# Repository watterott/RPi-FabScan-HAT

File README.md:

# RPi-FabScan-HAT
Raspberry Pi HAT (Hardware Attached on Top) to drive Stepper and Servo Motors or to build a 3D Laser Scanner.

Infos about the FabScan 3D-Scanner: http://www.fabscan.org

* Microchip ATmega328P with Arduino compatible Bootloader (optiboot)
* Sockets for Stepper Motor Drivers like StepStick or SilenStepStick
* Connectors for Servo Motors
* Laser control outputs
* [Raspberry Pi HAT](https://github.com/raspberrypi/hats) compatible (40 pin connector)
* Open-Source and released under the [Creative Commons Attribution Share-Alike License](https://creativecommons.org/licenses/by-sa/4.0/).
* **[Documentation on learn.watterott.com](https://learn.watterott.com)**

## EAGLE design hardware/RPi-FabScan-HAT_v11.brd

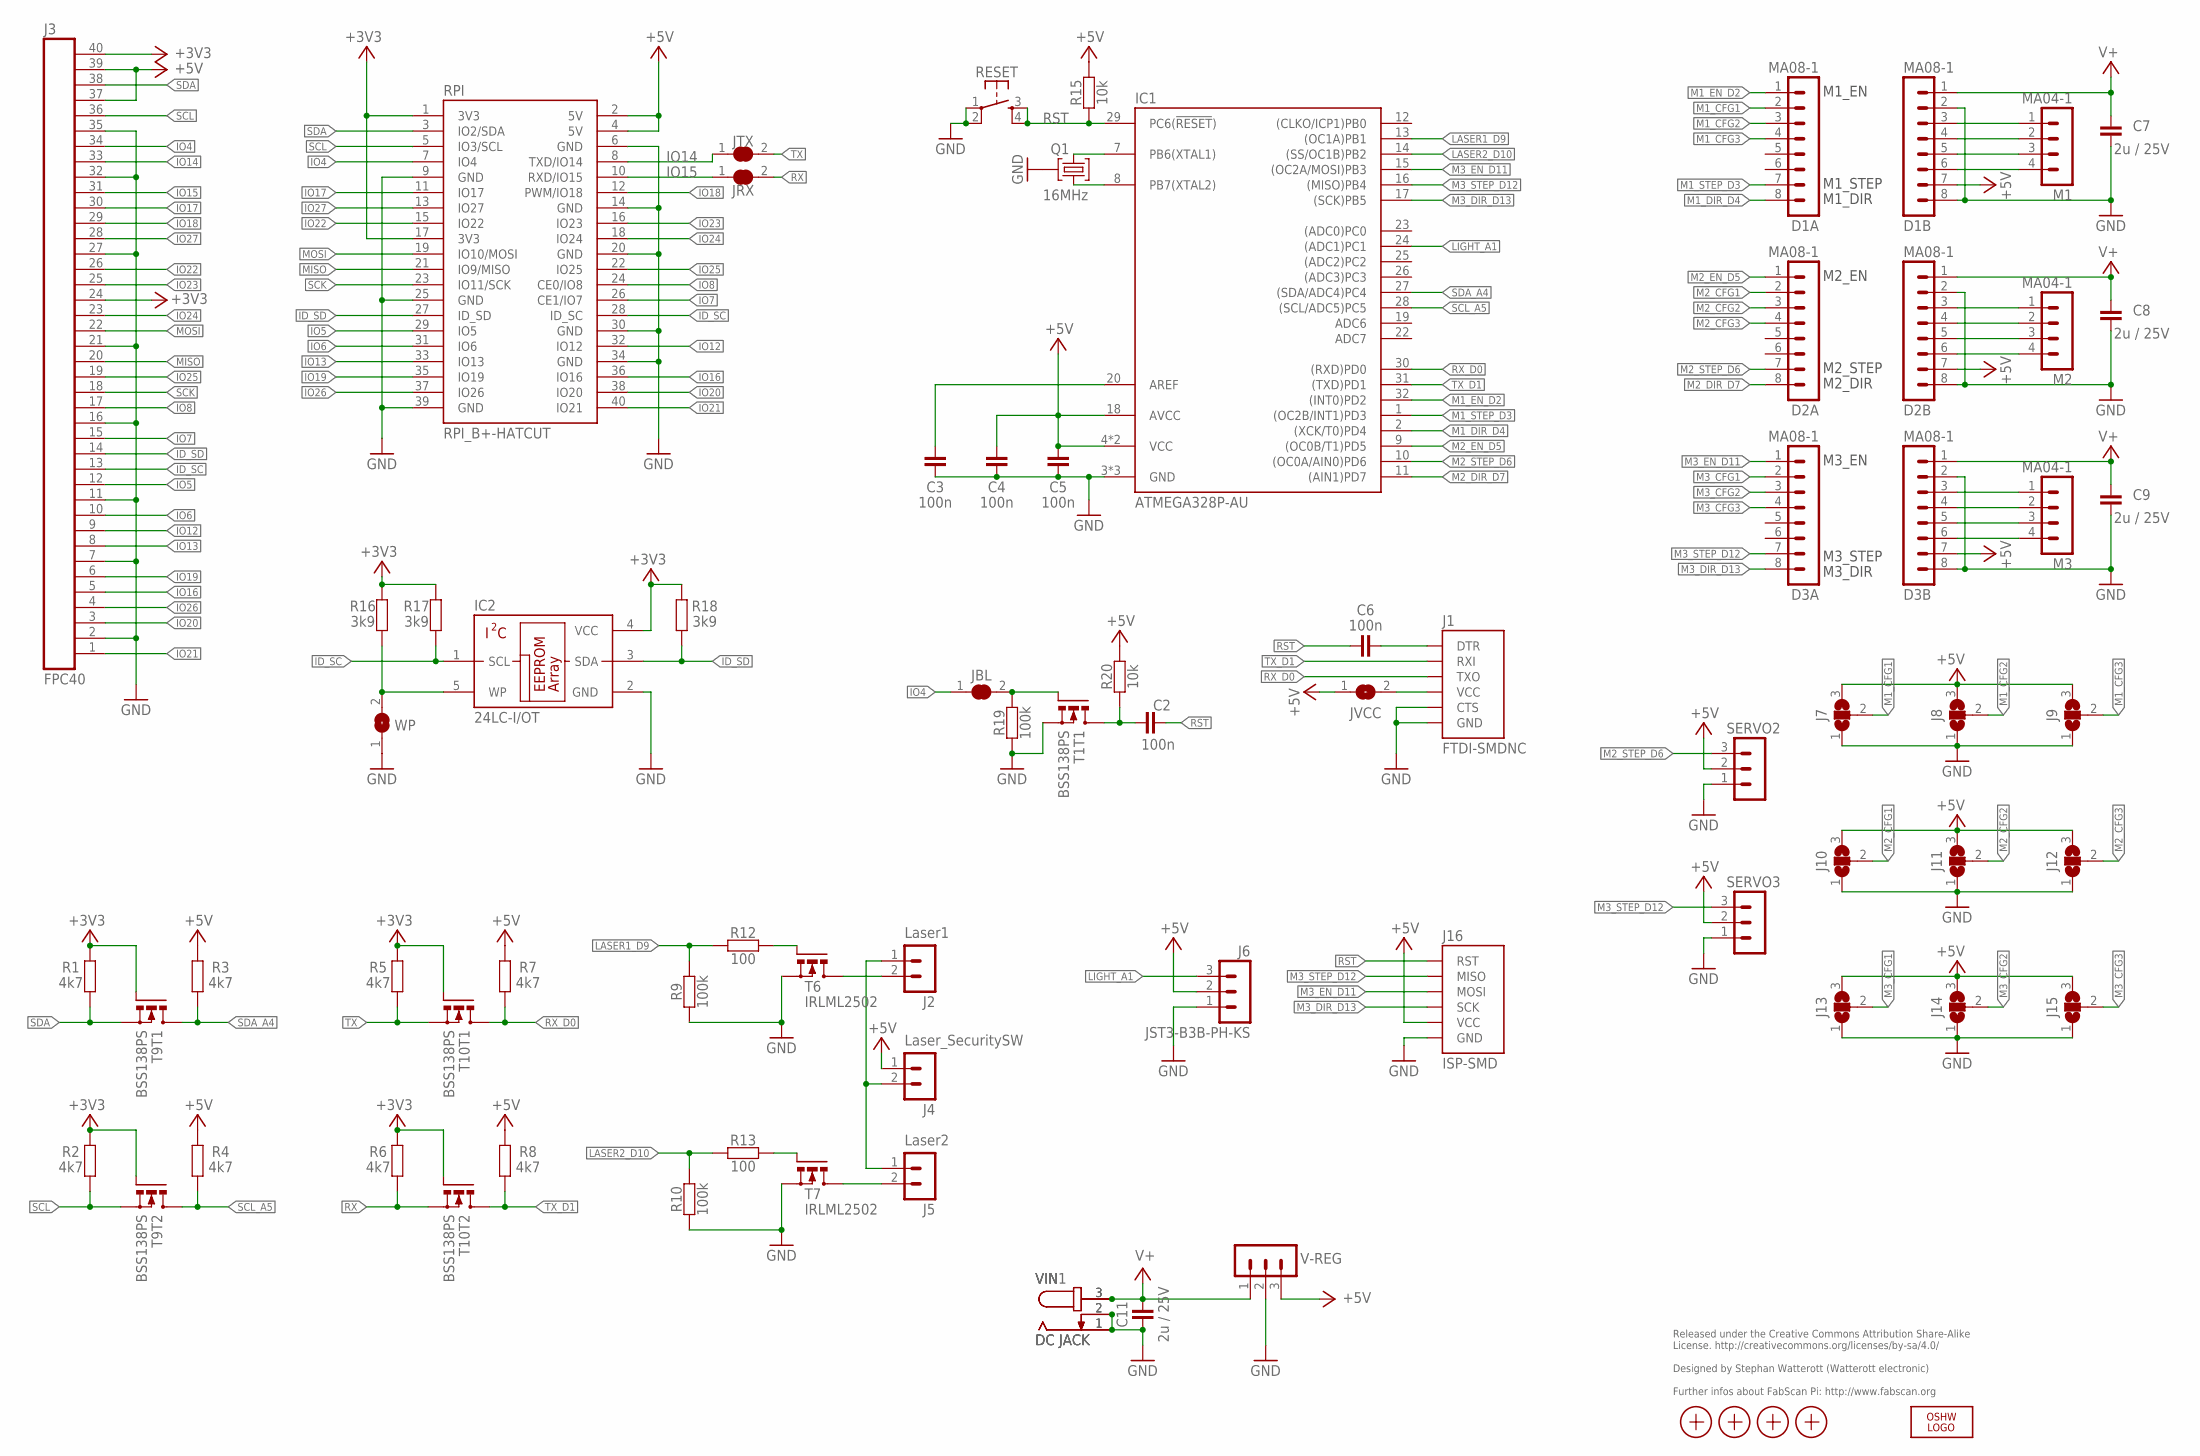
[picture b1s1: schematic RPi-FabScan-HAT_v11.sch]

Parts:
1, 2: PASSER-07; PASSER_07MM
C2, C3, C4, C5, C6: 100n; C0402
C7, C8, C9, C11: 2u / 25V; C1206
D1A, D1B, D2A, D2B, D3A, D3B: MA08-1
IC1: ATMEGA328P-AU; TQFP32
IC2: 24LC-I/OT; SOT23-5
J1: FTDI-SMDNC; FTDI_SMDNC
J2: Laser1; MA02-1
J3: FPC40; FPC40-0.5
J4: Laser_SecuritySW; MA02-1
J5: Laser2; MA02-1
J6: JST3-B3B-PH-KS; JST_B3B-PH-KS
J7, J8, J9, J10, J11, J12, J13, J14, J15: JUMPER3-0603-NC; JUMPER3-0603_NC
J16: ISP-SMD; ISP-2X3_SMD
JBL: JUMPER2-0402-NC; JUMPER2-0402_NC
JRX: JUMPER2-0402-NC; JUMPER2-0402_NC
JTX: JUMPER2-0402-NC; JUMPER2-0402_NC
JVCC: JUMPER2-0402-NC; JUMPER2-0402_NC
LOGO2: OSHW_LOGOX0100; OSHW_6X100
M1, M2, M3: MA04-1
Q1: 16MHz; CRYSTAL_32X13
R1, R2, R3, R4, R5, R6, R7, R8: 4k7; C0402
R9, R10, R19: 100k; C0402
R12, R13: 100; C0402
R15, R20: 10k; C0402
R16, R17, R18: 3k9; C0402
RESET: SW-TACTILE-PTS840P; SW_PTS840P
RPI: RPI_B+-HATCUT; RPI-B+HAT_CUTOUT
SERVO2, SERVO3: MA03-1
T1, T9, T10: BSS138PS; SOT363
T6, T7: IRLML2502; SOT23
V-REG: MA03-1
VIN, VIN1: DC JACK; DC-JACK
WP: JUMPER2-0402-NC; JUMPER2-0402_NC
X1, X4: PASSER-07; PASSER_07MM

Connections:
+3V3: IC2.4 (VCC), J3.24, J3.40, R1.1, R2.1, R5.1, R6.1, R16.2, R17.2, R18.2, RPI.1 (3V3), RPI.17 (3V3), T9.2 (G), T9.5 (G), T10.2 (G), T10.5 (G)
+5V: C4.2, C5.2, D1B.7, D2B.7, D3B.7, IC1.4 (VCC), IC1.6 (VCC), IC1.18 (AVCC), J3.37, J3.39, J4.1, J6.2, J7.3, J8.3, J9.3, J10.3, J11.3, J12.3, J13.3, J14.3, J15.3, J16.VCC, JVCC.1, R3.1, R4.1, R7.1, R8.1, R15.2, R20.2, RPI.2 (5V), RPI.4 (5V), SERVO2.2, SERVO3.2, V-REG.3
GND: C3.1, C4.1, C5.1, C7.1, C8.1, C9.1, C11.1, D1B.2, D1B.8, D2B.2, D2B.8, D3B.2, D3B.8, IC1.3 (GND), IC1.5 (GND), IC1.21 (GND), IC2.2 (GND), J1.1-GND (GND), J1.2-CTS (CTS), J3.2, J3.7, J3.11, J3.16, J3.21, J3.27, J3.32, J3.35, J6.1, J7.1, J8.1, J9.1, J10.1, J11.1, J12.1, J13.1, J14.1, J15.1, J16.GND, Q1.GND, R9.1, R10.1, R19.1, RESET.1, RESET.2, RPI.6 (GND), RPI.9 (GND), RPI.14 (GND), RPI.20 (GND), RPI.25 (GND), RPI.30 (GND), RPI.34 (GND), RPI.39 (GND), SERVO2.1, SERVO3.1, T1.1 (S), T6.2 (S), T7.2 (S), V-REG.2, VIN.1, VIN.2, VIN1.1, VIN1.2, WP.1
ID_SC: IC2.1 (SCL), J3.13, R17.1, RPI.28 (ID_SC)
ID_SD: IC2.3 (SDA), J3.14, R18.1, RPI.27 (ID_SD)
IO4: J3.34, JBL.1, RPI.7 (IO4)
IO5: J3.12, RPI.29 (IO5)
IO6: J3.10, RPI.31 (IO6)
IO7: J3.15, RPI.26 (CE1/IO7)
IO8: J3.17, RPI.24 (CE0/IO8)
IO12: J3.9, RPI.32 (IO12)
IO13: J3.8, RPI.33 (IO13)
IO14: J3.33, JTX.1, RPI.8 (TXD/IO14)
IO15: J3.31, JRX.1, RPI.10 (RXD/IO15)
IO16: J3.5, RPI.36 (IO16)
IO17: J3.30, RPI.11 (IO17)
IO18: J3.29, RPI.12 (PWM/IO18)
IO19: J3.6, RPI.35 (IO19)
IO20: J3.3, RPI.38 (IO20)
IO21: J3.1, RPI.40 (IO21)
IO22: J3.26, RPI.15 (IO22)
IO23: J3.25, RPI.16 (IO23)
IO24: J3.23, RPI.18 (IO24)
IO25: J3.19, RPI.22 (IO25)
IO26: J3.4, RPI.37 (IO26)
IO27: J3.28, RPI.13 (IO27)
LASER1_D9: IC1.13 ((OC1A)PB1), R9.2, R12.1
LASER2_D10: IC1.14 ((SS/OC1B)PB2), R10.2, R13.1
LIGHT_A1: IC1.24 ((ADC1)PC1), J6.3
M1_CFG1: D1A.2, J7.2
M1_CFG2: D1A.3, J8.2
M1_CFG3: D1A.4, J9.2
M1_DIR_D4: D1A.8, IC1.2 ((XCK/T0)PD4)
M1_EN_D2: D1A.1, IC1.32 ((INT0)PD2)
M1_STEP_D3: D1A.7, IC1.1 ((OC2B/INT1)PD3)
M2_CFG1: D2A.2, J10.2
M2_CFG2: D2A.3, J11.2
M2_CFG3: D2A.4, J12.2
M2_DIR_D7: D2A.8, IC1.11 ((AIN1)PD7)
M2_EN_D5: D2A.1, IC1.9 ((OC0B/T1)PD5)
M2_STEP_D6: D2A.7, IC1.10 ((OC0A/AIN0)PD6), SERVO2.3
M3_CFG1: D3A.2, J13.2
M3_CFG2: D3A.3, J14.2
M3_CFG3: D3A.4, J15.2
M3_DIR_D13: D3A.8, IC1.17 ((SCK)PB5), J16.SCK
M3_EN_D11: D3A.1, IC1.15 ((OC2A/MOSI)PB3), J16.MOSI
M3_STEP_D12: D3A.7, IC1.16 ((MISO)PB4), J16.MISO, SERVO3.3
MISO: J3.20, RPI.21 (IO9/MISO)
MOSI: J3.22, RPI.19 (IO10/MOSI)
unnamed: IC1.7 (PB6(XTAL1)), Q1.2
unnamed: IC1.8 (PB7(XTAL2)), Q1.1
unnamed: D3B.3, M3.1
unnamed: C3.2, IC1.20 (AREF)
unnamed: R12.2, T6.1 (G)
unnamed: R13.2, T7.1 (G)
unnamed: C6.1, J1.6-DTR (DTR)
unnamed: J2.1, J4.2, J5.1
unnamed: JBL.2, R19.2, T1.2 (G)
unnamed: C2.2, R20.1, T1.6 (D)
unnamed: J2.2, T6.3 (D)
unnamed: D3B.4, M3.2
unnamed: D3B.5, M3.3
unnamed: D3B.6, M3.4
unnamed: D2B.3, M2.1
unnamed: D2B.4, M2.2
unnamed: D2B.5, M2.3
unnamed: D2B.6, M2.4
unnamed: D1B.3, M1.1
unnamed: D1B.4, M1.2
unnamed: D1B.5, M1.3
unnamed: D1B.6, M1.4
unnamed: J5.2, T7.3 (D)
unnamed: IC2.5 (WP), R16.1, WP.2
RST: C2.1, C6.2, IC1.29 (PC6(!RESET!)), J16.RST, R15.1, RESET.3 (S1), RESET.4 (S2)
RX: JRX.2, R6.2, T10.4 (S)
RX_D0: IC1.30 ((RXD)PD0), J1.4-TXO (TXO), R7.2, T10.6 (D)
SCK: J3.18, RPI.23 (IO11/SCK)
SCL: J3.36, R2.2, RPI.5 (IO3/SCL), T9.4 (S)
SCL_A5: IC1.28 ((SCL/ADC5)PC5), R4.2, T9.3 (D)
SDA: J3.38, R1.2, RPI.3 (IO2/SDA), T9.1 (S)
SDA_A4: IC1.27 ((SDA/ADC4)PC4), R3.2, T9.6 (D)
TX: JTX.2, R5.2, T10.1 (S)
TX_D1: IC1.31 ((TXD)PD1), J1.5-RXI (RXI), R8.2, T10.3 (D)
V+: C7.2, C8.2, C9.2, C11.2, D1B.1, D2B.1, D3B.1, V-REG.1, VIN.3, VIN1.3
VCC_FTDI: J1.3-VCC (VCC), JVCC.2

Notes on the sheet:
M1_EN
M1_STEP
M1_DIR
M2_EN
M2_STEP
M2_DIR
M3_EN
M3_STEP
M3_DIR
Released under the Creative Commons Attribution Share-Alike License. http://creativecommons.org/licenses/by-sa/4.0/ Designed by Stephan Watterott (Watterott electronic) Further infos about FabScan Pi: http://www.fabscan.org

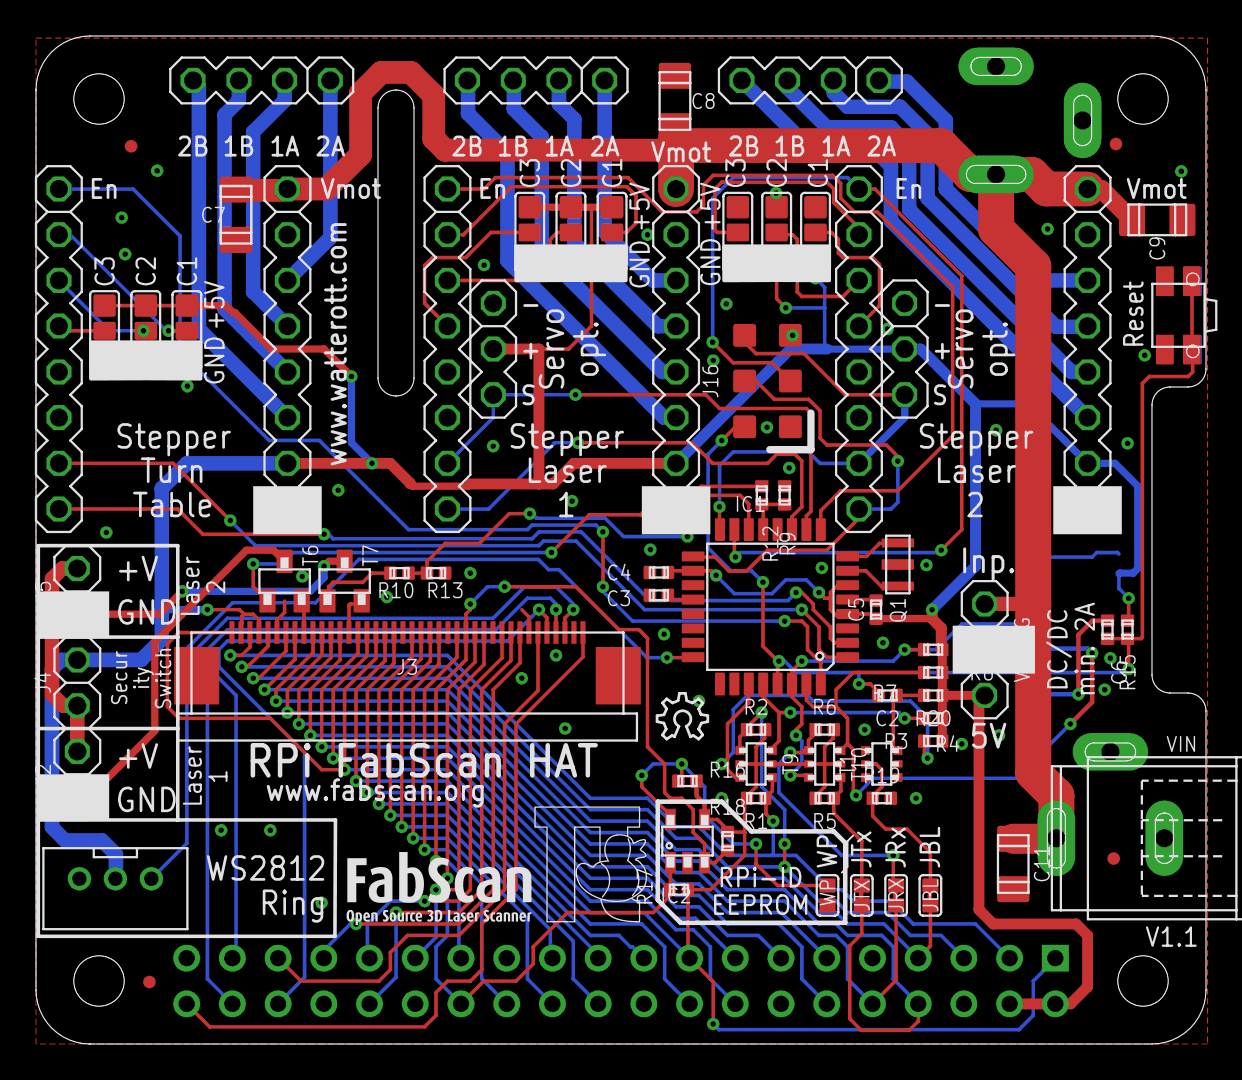
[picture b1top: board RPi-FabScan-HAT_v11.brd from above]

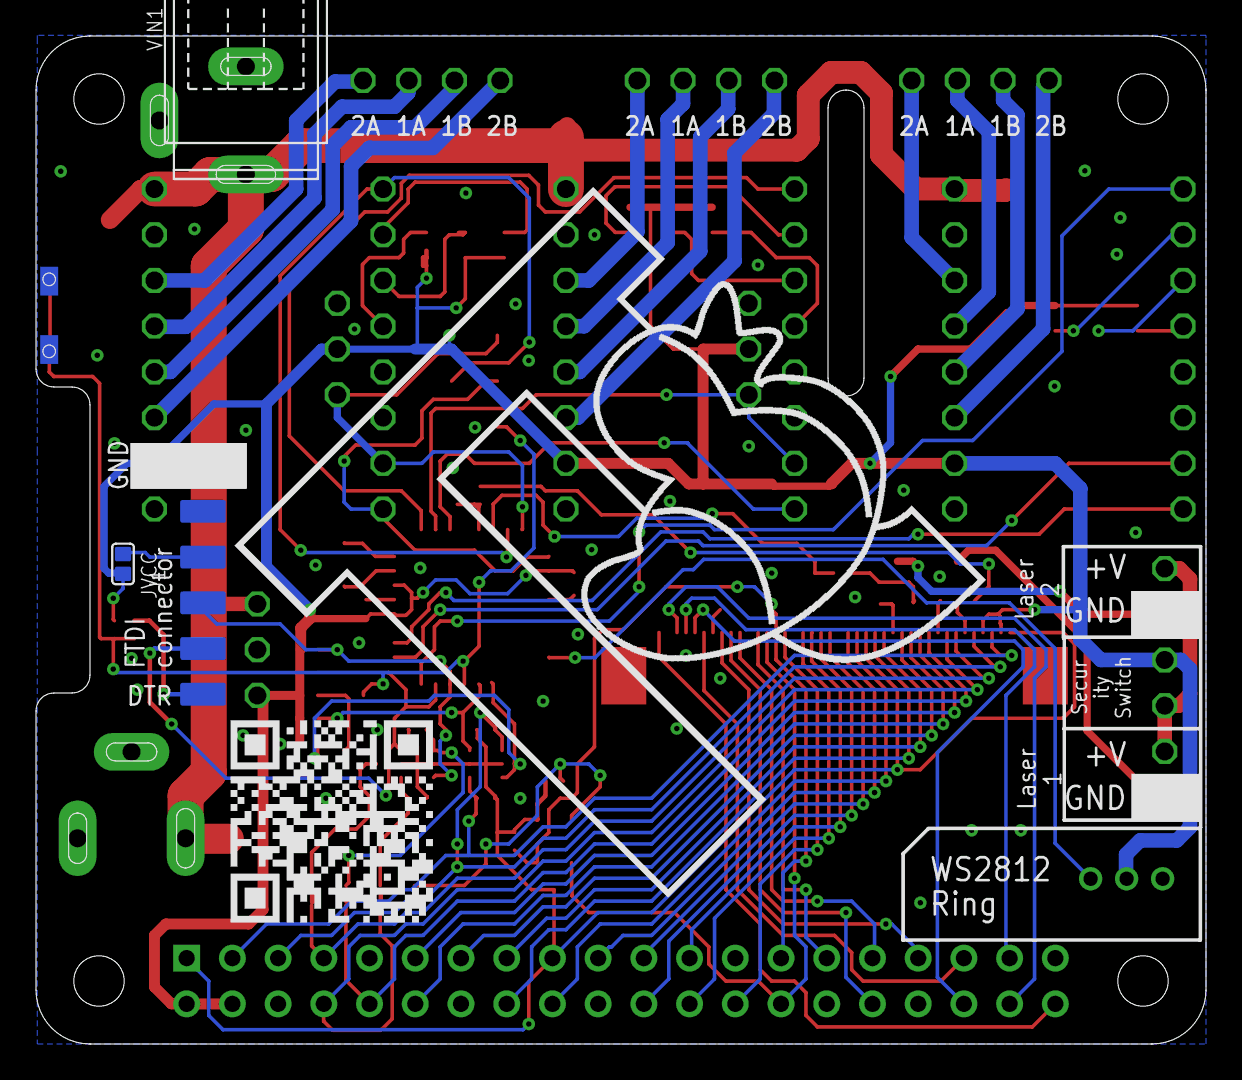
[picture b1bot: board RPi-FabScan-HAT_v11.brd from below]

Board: 2 copper layers, 65.0 x 56.0 mm, 77 parts (3 on the bottom side), 85 nets.

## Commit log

2020-10-23 added V1.1
2020-10-23 added V1.2
2021-04-12 convert to Eagle 7
